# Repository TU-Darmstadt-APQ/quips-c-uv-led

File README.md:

# QUIPS-C UV-LEDs PCB and Mounting Apparatus
UV-LEDs intended for QUIPS-C experiment, includes CAD-models of mount and PCB.\
Adsorption of Rubidium atoms on the vacuum chamber surfaces can lead to stray electric fields, negatively impacting the Rydberg transition. Ionisation by UV light aims to suppress this effect.

Available Files
-------
This repository includes:
- FreeCAD-files containing the model for the mounting apparatus.
- KiCAD-files containing the PCB design housing the LEDs. Additional resources such as Gerber files will be added in the future.

Mounting Requirements
-------
The rectangular PCB is to be mounted via 2 M3-screws onto the aluminium mount. Heat transfer is maintained by thermal paste. The mount itself is fixated onto existing mounting posts attached to the QUIPS-C vacuum chamber.

Parts
-------
- LED: Luminus Devices SST-08-UV-A40H-F365-00 (5 pieces)
- Resistor: Vishay CRCW12184R02FKEKHP
- Connector: JST_PH_B2B-PH-K_1x02_P2.00mm_Vertical

Power Specifications
-------
LED specifications:
- central wavelength: **365 nm**
- absolute maximum forward current: **1 A**
- absolute maximum junction temperature: **100 °C**
- radiometric flux at 0.5A: **>810 mW**
- maximum forward voltage: **3.6 V**

Resistor specifications:
- resistance: **4 Ohm**
- maximum power: **3.5 W**

Overall design specifications:
- nominal operation at **20 V / 0.5A**, power draw: **10 W**
- total radiometrix flux: **~4 W**
- heating power: **~6 W**

License
-------
This work is released under the CERN-OHL-W.\
See [https://ohwr.org/cern_ohl_w_v2.pdf](https://ohwr.org/cern_ohl_w_v2.pdf) or the included LICENSE file for more information.

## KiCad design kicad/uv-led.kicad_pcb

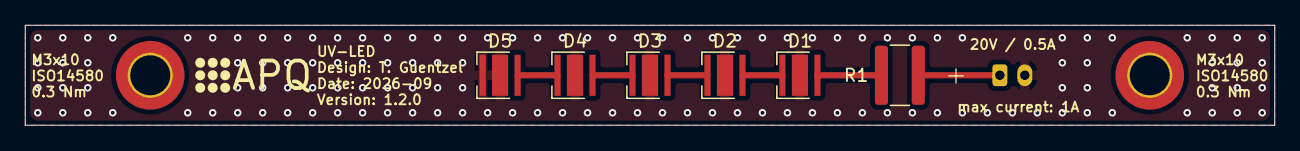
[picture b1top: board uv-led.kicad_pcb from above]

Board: 2 copper layers, 100.0 x 8.0 mm, 10 parts (1 on the bottom side), 7 nets.

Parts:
D1, D2, D3, D4, D5: SST-08H; LED_Cree-XHP35
H1, H2: MountingHole_Pad; MountingHole_3.2mm_M3_ISO14580_Pad_TopOnly
J1: JST_PH_B2B-PH-K_1x02_P2.00mm_Vertical
LOGO1: Logo_APQ; APQ-Logo_small
R1: 4R; R_1218_3246Metric

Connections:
+20V: J1.1, R1.2
GND: D1.3 (PAD), D2.3 (PAD), D3.3 (PAD), D4.3 (PAD), D5.1 (K), D5.3 (PAD), J1.2
unnamed: D1.2 (A), R1.1
unnamed: D1.1 (K), D2.2 (A)
unnamed: D2.1 (K), D3.2 (A)
unnamed: D3.1 (K), D4.2 (A)
unnamed: D4.1 (K), D5.2 (A)

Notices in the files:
kicad/uv-led.kicad_pcb:
Copyright (©) 2026, Tom Güntzel
Licensed under CERN OHL-W v2.0
